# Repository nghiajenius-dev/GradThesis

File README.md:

# GradThesis
Integrated Indoor Positioning and Trajectory Controller of Quadcopter
## Project Description: 
https://discuss.ardupilot.org/t/integrated-indoor-positioning-and-trajectory-control-of-quadcopter/25720

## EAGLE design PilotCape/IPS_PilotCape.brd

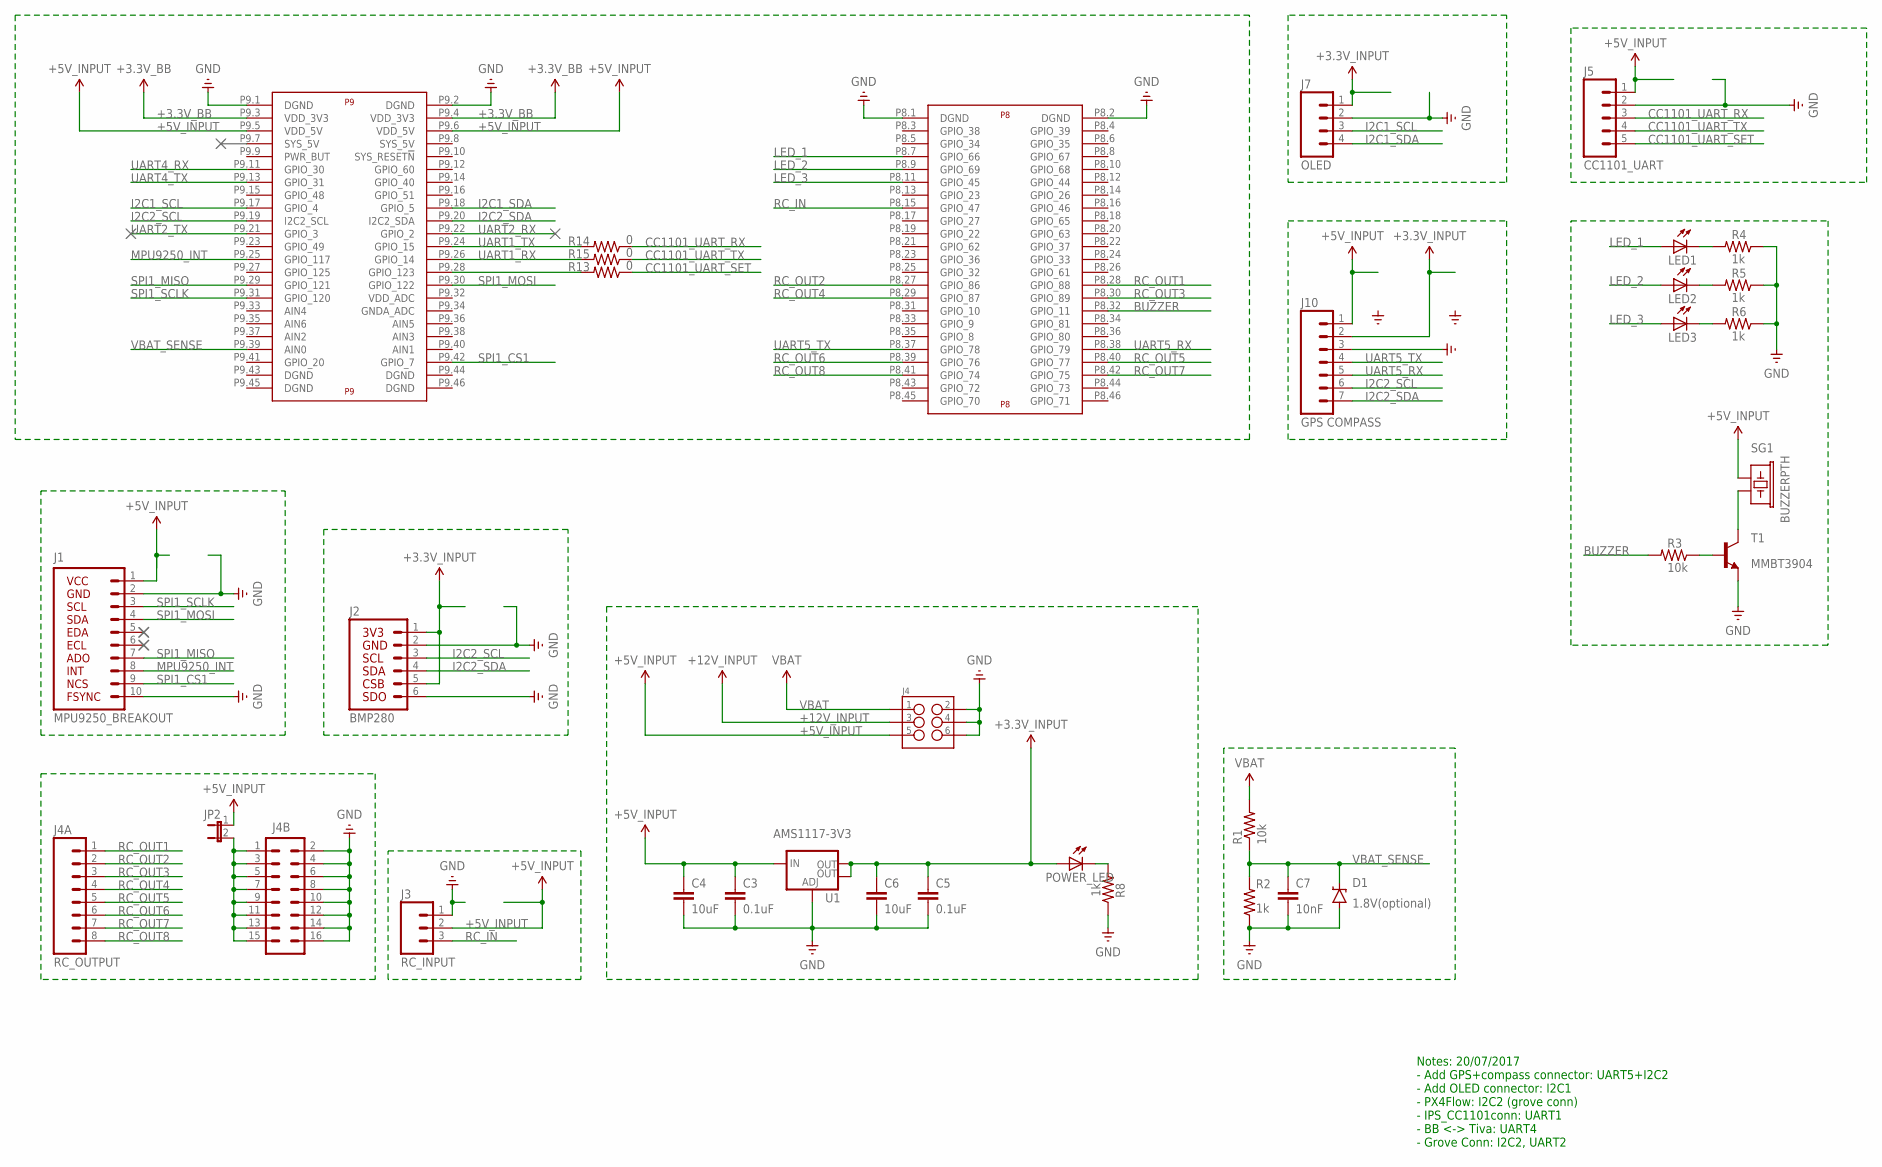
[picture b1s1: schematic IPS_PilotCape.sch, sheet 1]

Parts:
C3, C5: 0.1uF; 0603-CAP
C4, C6: 10uF; 1210
C7: 10nF; 0603-CAP
D1: 1.8V(optional); SOD-323
J1: MPU9250_BREAKOUT
J2: BMP280
J3: RC_INPUT; 1X03
J4: M03X2NO_SILK; 2X3-NS
J4A: RC_OUTPUT; 1X08
J4B: M08X2; 2X8
J5: CC1101_UART; 1X05
J7: OLED; 1X04
J10: GPS COMPASS; 1X07
JP2: JUMPER-2PTH; 1X02
LED1, LED2, LED3: LEDCHIPLED_0805; CHIPLED_0805
POWER_LED: LEDCHIPLED_0805; CHIPLED_0805
R1, R3: 10k; R0603
R2, R4, R5, R6, R8: 1k; R0603
R13, R14, R15: 0; R0603
SG1: BUZZERPTH; BUZZER-12MM
T1: MMBT3904; SOT23-BEC
U1: AMS1117-3V3; SOT223
U$2: BEAGLE_BONE_BLACK_CAPE

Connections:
+3.3V_BB: U$2.P9.3 (VDD_3V3), U$2.P9.4 (VDD_3V3)
+3.3V_INPUT: C5.1, C6.1, J2.1, J2.5, J7.1, J10.2, POWER_LED.A, U1.2 (OUT), U1.4 (OUT); also elsewhere on the board
+5V_INPUT: C3.1, C4.1, J1.1, J3.2, J4.5, J5.1, J10.1, JP2.1, SG1.+ (1), U1.3 (IN), U$2.P9.5 (VDD_5V), U$2.P9.6 (VDD_5V); also elsewhere on the board
+12V_INPUT: J4.3; also elsewhere on the board
BUZZER: R3.2, U$2.P8.32 (GPIO_11)
CC1101_UART_RX: J5.3, R14.1; also elsewhere on the board
CC1101_UART_SET: J5.5, R13.1
CC1101_UART_TX: J5.4, R15.1; also elsewhere on the board
GND: C3.2, C4.2, C5.2, C6.2, C7.2, D1.A, J1.2, J1.10, J2.2, J2.6, J3.1, J4.2, J4.4, J4.6, J4B.2, J4B.4, J4B.6, J4B.8, J4B.10, J4B.12, J4B.14, J4B.16, J5.2, J7.2, J10.3, R2.1, R4.1, R5.1, R6.1, R8.1, T1.E, U1.1 (ADJ), U$2.P8.1 (DGND), U$2.P8.2 (DGND), U$2.P9.1 (DGND), U$2.P9.2 (DGND); also elsewhere on the board
I2C1_SCL: J7.3, U$2.P9.17 (GPIO_4)
I2C1_SDA: J7.4, U$2.P9.18 (GPIO_5)
I2C2_SCL: J2.3, J10.6, U$2.P9.19 (I2C2_SCL)
I2C2_SDA: J2.4, J10.7, U$2.P9.20 (I2C2_SDA)
LED_1: LED1.A, U$2.P8.7 (GPIO_66)
LED_2: LED2.A, U$2.P8.9 (GPIO_69)
LED_3: LED3.A, U$2.P8.11 (GPIO_45)
MPU9250_INT: J1.8, U$2.P9.25 (GPIO_117)
unnamed: J4B.1, J4B.3, J4B.5, J4B.7, J4B.9, J4B.11, J4B.13, J4B.15, JP2.2
unnamed: SG1.- (2), T1.C
unnamed: R3.1, T1.B
unnamed: LED1.C, R4.2
unnamed: LED2.C, R5.2
unnamed: LED3.C, R6.2
unnamed: POWER_LED.C, R8.2
unnamed: R13.2, U$2.P9.28 (GPIO_123)
RC_IN: J3.3, U$2.P8.15 (GPIO_47)
RC_OUT1: J4A.1, U$2.P8.28 (GPIO_88)
RC_OUT2: J4A.2, U$2.P8.27 (GPIO_86)
RC_OUT3: J4A.3, U$2.P8.30 (GPIO_89)
RC_OUT4: J4A.4, U$2.P8.29 (GPIO_87)
RC_OUT5: J4A.5, U$2.P8.40 (GPIO_77)
RC_OUT6: J4A.6, U$2.P8.39 (GPIO_76)
RC_OUT7: J4A.7, U$2.P8.42 (GPIO_75)
RC_OUT8: J4A.8, U$2.P8.41 (GPIO_74)
SPI1_CS1: J1.9, U$2.P9.42 (GPIO_7)
SPI1_MISO: J1.7, U$2.P9.29 (GPIO_121)
SPI1_MOSI: J1.4, U$2.P9.30 (GPIO_122)
SPI1_SCLK: J1.3, U$2.P9.31 (GPIO_120)
UART1_RX: R15.2, U$2.P9.26 (GPIO_14)
UART1_TX: R14.2, U$2.P9.24 (GPIO_15)
UART2_RX: U$2.P9.22 (GPIO_2)
UART2_TX: U$2.P9.21 (GPIO_3)
UART4_RX: U$2.P9.11 (GPIO_30); also elsewhere on the board
UART4_TX: U$2.P9.13 (GPIO_31); also elsewhere on the board
UART5_RX: J10.5, U$2.P8.38 (GPIO_79)
UART5_TX: J10.4, U$2.P8.37 (GPIO_78)
VBAT: J4.1, R1.2
VBAT_SENSE: C7.1, D1.C, R1.1, R2.2, U$2.P9.39 (AIN0)

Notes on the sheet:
Notes: 20/07/2017 - Add GPS+compass connector: UART5+I2C2 - Add OLED connector: I2C1 - PX4Flow: I2C2 (grove conn) - IPS_CC1101conn: UART1 - BB <-> Tiva: UART4 - Grove Conn: I2C2, UART2

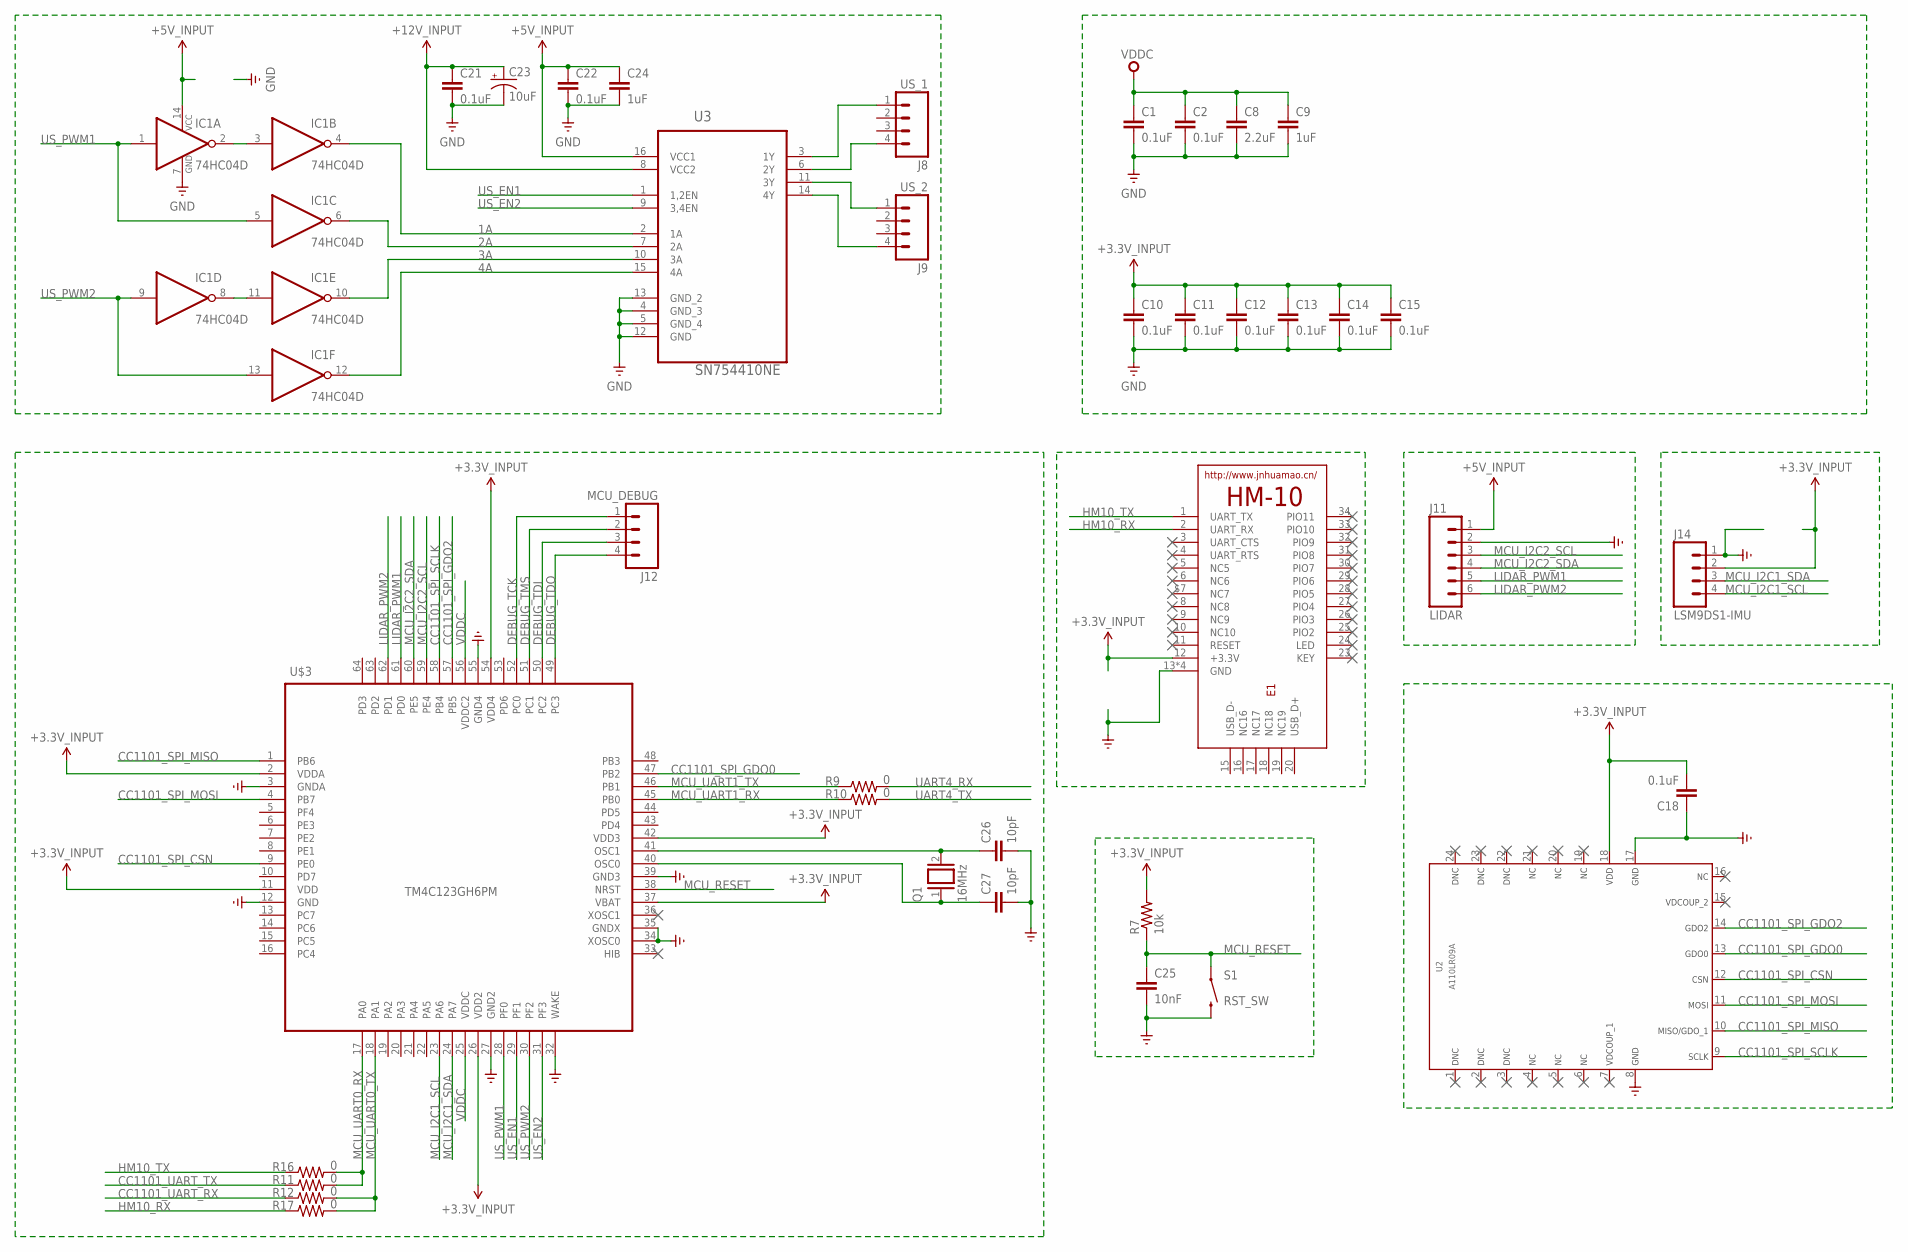
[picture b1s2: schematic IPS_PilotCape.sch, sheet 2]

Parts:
C1, C2, C10, C11, C12, C13, C14, C15, C18, C21, C22: 0.1uF; 0603-CAP
C8: 2.2uF; 0603-CAP
C9, C24: 1uF; 0603-CAP
C23: 10uF; EIA3216
C25: 10nF; 0603-CAP
C26, C27: 10pF; 0603-CAP
E1: HM-10-BOARD; 26.9X13X2.2_BOARD
IC1: 74HC04D; SO14
J8: US_1; 1X04
J9: US_2; 1X04
J11: LIDAR; 1X06
J12: MCU_DEBUG; 1X04
J14: LSM9DS1-IMU; 1X04
Q1: 16MHz; QS
R7: 10k; R0603
R9, R10, R11, R12, R16, R17: 0; R0603
S1: RST_SW; TACTILE-SWITCH-1101NE
U2: A110LR09A
U3: SN754410NE; DIP254P762X508-16
U$3: TM4C123GH6PM; LQPF-64

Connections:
1A: IC1.4 (O), U3.2 (1A)
2A: IC1.6 (O), U3.7 (2A)
3A: IC1.10 (O), U3.10 (3A)
4A: IC1.12 (O), U3.15 (4A)
+3.3V_INPUT: C10.1, C11.1, C12.1, C13.1, C14.1, C15.1, C18.2, E1.12 (+3.3V), J14.2, R7.2, U2.18, U$3.2 (VDDA), U$3.11 (VDD), U$3.26 (VDD2), U$3.37 (VBAT), U$3.42 (VDD3), U$3.54 (VDD4); also elsewhere on the board
+5V_INPUT: C22.1, C24.1, IC1.14 (VCC), J11.1, U3.16 (VCC1); also elsewhere on the board
+12V_INPUT: C21.1, C23.A (+), U3.8 (VCC2); also elsewhere on the board
CC1101_SPI_CSN: U2.12, U$3.9 (PE0)
CC1101_SPI_GDO0: U2.13, U$3.47 (PB2)
CC1101_SPI_GDO2: U2.14, U$3.57 (PB5)
CC1101_SPI_MISO: U2.10, U$3.1 (PB6)
CC1101_SPI_MOSI: U2.11, U$3.4 (PB7)
CC1101_SPI_SCLK: U2.9, U$3.58 (PB4)
CC1101_UART_RX: R12.1; also elsewhere on the board
CC1101_UART_TX: R11.1; also elsewhere on the board
DEBUG_TCK: J12.1, U$3.52 (PC0)
DEBUG_TDI: J12.3, U$3.50 (PC2)
DEBUG_TDO: J12.4, U$3.49 (PC3)
DEBUG_TMS: J12.2, U$3.51 (PC1)
GND: C1.2, C2.2, C8.2, C9.2, C10.2, C11.2, C12.2, C13.2, C14.2, C15.2, C18.1, C21.2, C22.2, C23.C (-), C24.2, C25.2, C26.2, C27.2, E1.13 (GND), E1.14 (GND), E1.21 (GND), E1.22 (GND), IC1.7 (GND), J11.2, J14.1, S1.2, U2.8, U2.17, U3.4 (GND_3), U3.5 (GND_4), U3.12 (GND), U3.13 (GND_2), U$3.3 (GNDA), U$3.12 (GND), U$3.27 (GND2), U$3.32 (WAKE), U$3.34 (XOSC0), U$3.35 (GNDX), U$3.39 (GND3), U$3.55 (GND4); also elsewhere on the board
HM10_RX: E1.2 (UART_RX), R17.1
HM10_TX: E1.1 (UART_TX), R16.1
LIDAR_PWM1: J11.5, U$3.61 (PD0)
LIDAR_PWM2: J11.6, U$3.62 (PD1)
MCU_I2C1_SCL: J14.4, U$3.23 (PA6)
MCU_I2C1_SDA: J14.3, U$3.24 (PA7)
MCU_I2C2_SCL: J11.3, U$3.59 (PE4)
MCU_I2C2_SDA: J11.4, U$3.60 (PE5)
MCU_RESET: C25.1, R7.1, S1.1, U$3.38 (NRST)
MCU_UART0_RX: R11.2, R16.2, U$3.17 (PA0)
MCU_UART0_TX: R12.2, R17.2, U$3.18 (PA1)
MCU_UART1_RX: R10.1, U$3.45 (PB0)
MCU_UART1_TX: R9.1, U$3.46 (PB1)
unnamed: J8.1, U3.3 (1Y)
unnamed: J8.4, U3.6 (2Y)
unnamed: IC1.2 (O), IC1.3 (I)
unnamed: IC1.8 (O), IC1.11 (I)
unnamed: J9.1, U3.11 (3Y)
unnamed: J9.4, U3.14 (4Y)
unnamed: C26.1, Q1.2, U$3.41 (OSC1)
unnamed: C27.1, Q1.1, U$3.40 (OSC0)
UART4_RX: R9.2; also elsewhere on the board
UART4_TX: R10.2; also elsewhere on the board
US_EN1: U3.1 (1,2EN), U$3.29 (PF1)
US_EN2: U3.9 (3,4EN), U$3.31 (PF3)
US_PWM1: IC1.1 (I), IC1.5 (I), U$3.28 (PF0)
US_PWM2: IC1.9 (I), IC1.13 (I), U$3.30 (PF2)
VDDC: C1.1, C2.1, C8.1, C9.1, U$3.25 (VDDC), U$3.56 (VDDC2)

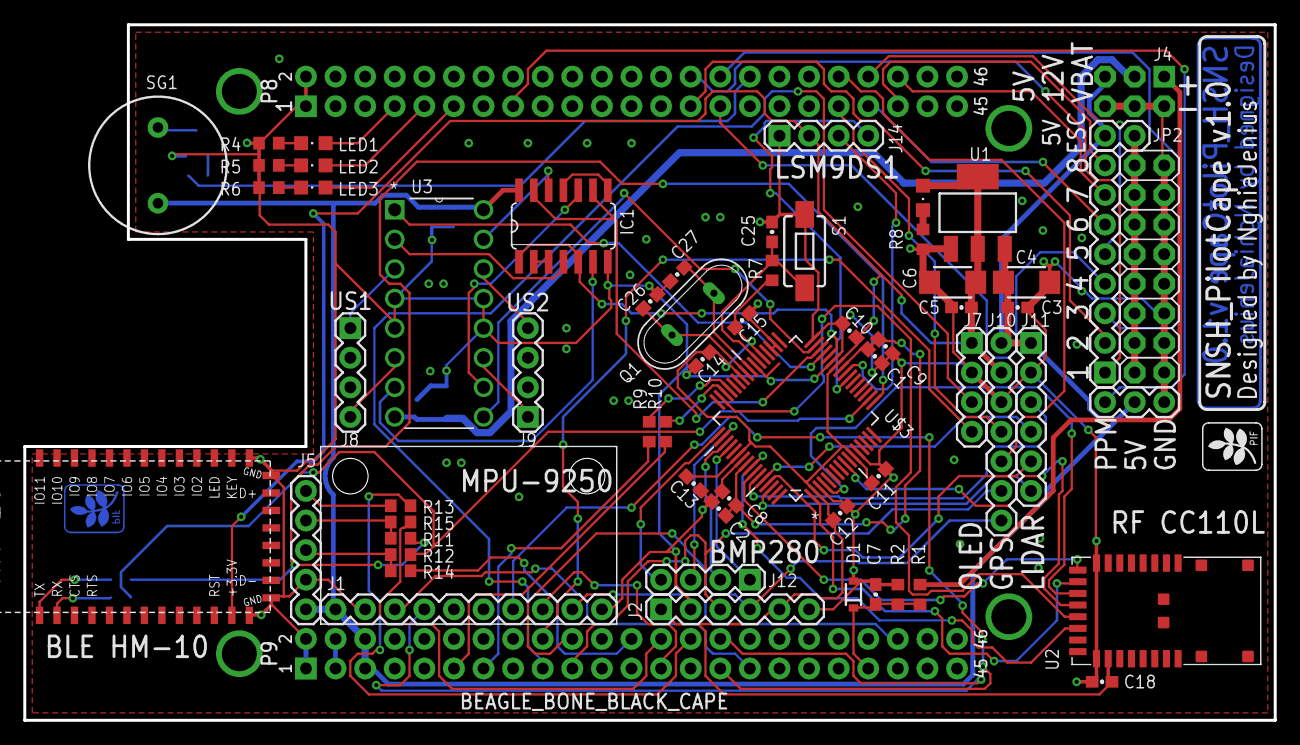
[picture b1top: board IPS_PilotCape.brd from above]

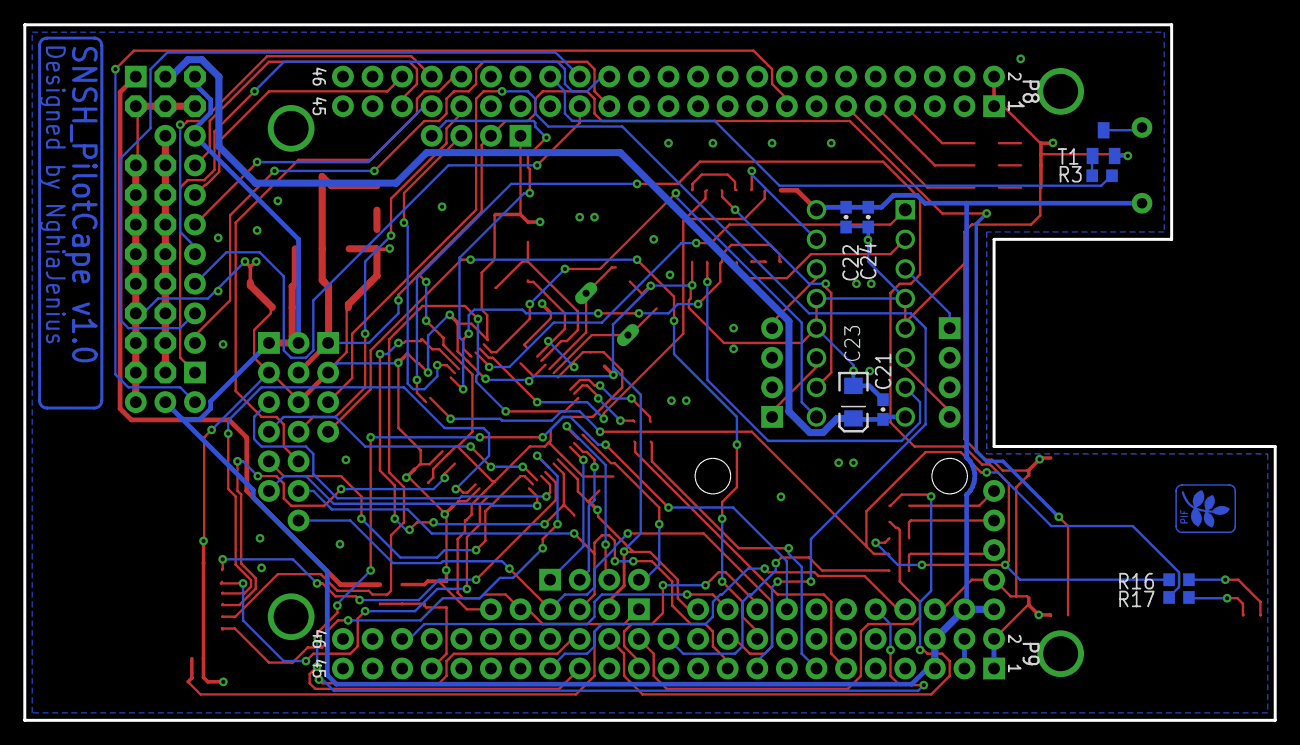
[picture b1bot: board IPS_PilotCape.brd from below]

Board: 2 copper layers, 107.3 x 59.7 mm, 73 parts (9 on the bottom side), 86 nets.

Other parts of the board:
U$1: PIF_SSTOP_5MM
U$4: PIF_LOGO_5X5MM

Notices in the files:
parts and their libraries:
SparkFun-Connectors: Licensing: Creative Commons ShareAlike 4.0 International - https://creativecommons.org/licenses/by-sa/4.0
ports: Copyright (C) 2008, Bob Starr
